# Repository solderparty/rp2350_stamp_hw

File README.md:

# The RP2350 Stamp

The Stamp was created to allow you to use the **Raspberry Pi RP2350A** in your designs without having to solder small-pitch QFN chips or worry about lots of external circuitry.

The RP2350 Stamp is pad-compatible with our previous RP2040 Stamp.

All you need to get you started is a 5V supply or a LiPo battery. The Stamp will take care of the charging and switching the power sources.

The castellated edges with **2mm pitch** can be hand-soldered directly to a Carrier board, used with pin headers for more flexibility, or connected without soldering using [FlexyPins](https://flexypin.solder.party), which are spring connectors designed for modules with castellated edges. You can find footprints for many PCB programs [here](https://github.com/solderparty/rp2xxx_stamp_footprints).

At only **1 by 1 inch**, the Stamp packs a lot of features:
* **16MB of FLASH**
* **500mA 3.3V LDO**
* **All 30 GPIOs broken out**
* LiPo supply and charging circuit (with charging LED)
* USB broken out
* SWD broken out
* Reset Button
* Bootsel Button
* 12MHz crystal

and of course, everything that comes with the Raspberry Pi RP2350 itself:
* Dual core ARM Cortex-M33 or Hazard3 @ 150MHz
* 520kB SRAM
* 2 UARTs
* 2 SPIs
* 2 I2Cs
* 24 PWM channels
* 12 PIO state machines
* 1 HSTX peripheral
* USB with Host and Device support

The RP2350 comes with a pre-programmed ROM UF2 Bootloader, by pulling the BOOTSEL pin low and resetting, or by double-pressing the RESET button (if the FW supports it), you can upload new firmware using the USB disk drive.

In addition to the Stamps we also offer a few reference designs, see the Carriers in the [Stamp-related category](https://docs.solder.party/rp2xxx-stamp-related) as well as our [Flux projects](https://docs.solder.party/flux).

The CircuitPython firmware for the Stamp comes with a built-in board files for the Carriers, for example you can access the RP2040 Stamp Carrier pins and interfaces by using `import stamp_carrier_board as board`. See [here](https://github.com/adafruit/circuitpython/tree/main/ports/raspberrypi/boards/solderparty_rp2040_stamp) for all the available Carrier board files.

# Links

For more information visit https://rp2350-stamp.solder.party/

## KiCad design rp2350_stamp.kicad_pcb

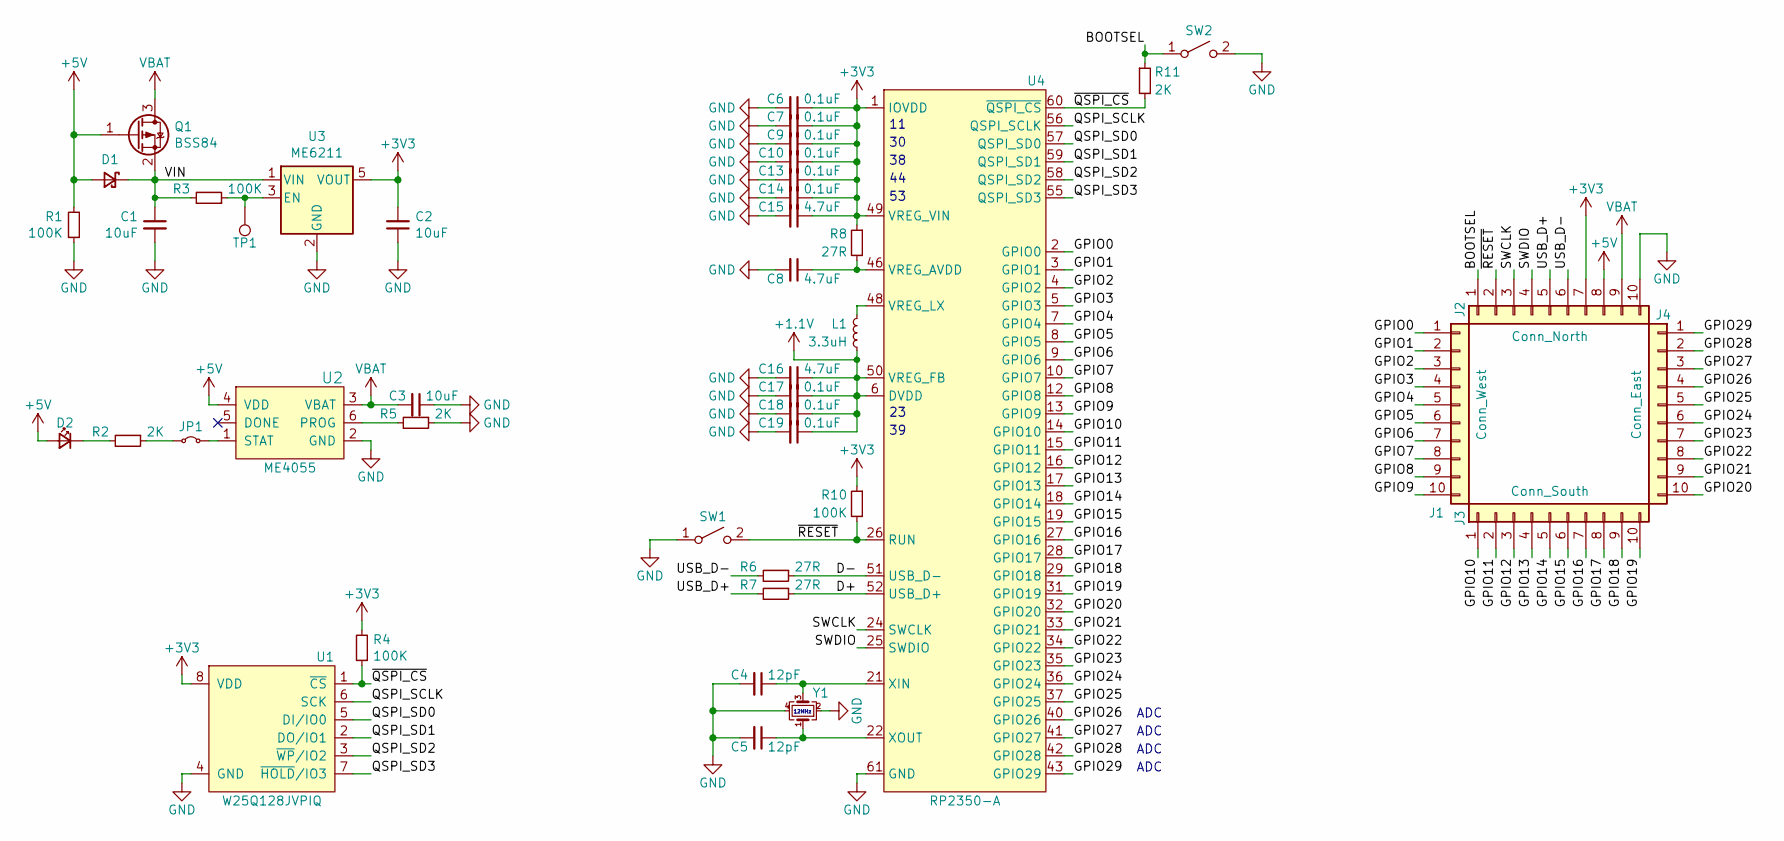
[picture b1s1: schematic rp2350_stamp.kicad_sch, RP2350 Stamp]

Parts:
C1, C2, C3: 10uF; C_0603_1608Metric
C4, C5: 12pF; C_0603_1608Metric
C6, C7, C9, C10, C13, C14, C17, C18, C19: 0.1uF; C_0603_1608Metric
C8, C15, C16: 4.7uF; C_0603_1608Metric
D1: D_Schottky_Small; D_SOD-323; LCSC C114023
D2: LED_CHR; LED_0603_1608Metric
J1: Conn_West; Castellated_1x10_P2.00mm_Vertical
J2: Conn_North; Castellated_1x10_P2.00mm_Vertical
J3: Conn_South; Castellated_1x10_P2.00mm_Vertical
J4: Conn_East; Castellated_1x10_P2.00mm_Vertical
JP1: SJ_STAT_LED; SolderJumper-2_P1.3mm_Bridged_RoundedPad1.0x1.5mm
L1: 3.3uH; L_Wuerth_MAPI-2512; LCSC C5832359
Q1: BSS84; SOT-23; LCSC C85202
R1, R3, R4, R10: 100K; R_0603_1608Metric
R2, R5, R11: 2K; R_0603_1608Metric
R6, R7, R8: 27R; R_0603_1608Metric
SW1: SW_RESET; SW_SPST_B3U-1000P; LCSC C561514
SW2: SW_BOOTSEL; SW_SPST_B3U-1000P; LCSC C561514
TP1: TP_LDO_EN; TestPoint_Pad_D1.5mm
U1: W25Q128JVPIQ; WSON-8-1EP_6x5mm_P1.27mm_EP3.4x4mm; LCSC C190862
U2: ME4055; SOT-23-6; LCSC C82121
U3: ME6211; SOT-23-5; LCSC C82942
U4: RP2350-A; QFN-60_EP_7x7_Pitch0.4mm
Y1: CM4012M00012001; Crystal_SMD_2520-4Pin_2.5x2.0mm; LCSC C7294611

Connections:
+1.1V: C16.1, C17.1, C18.1, C19.1, L1.1, U4.6 (DVDD), U4.23 (DVDD), U4.39 (DVDD), U4.50 (VREG_FB)
+3V3: C2.2, C6.1, C7.1, C9.1, C10.1, C13.1, C14.1, C15.1, J2.7, R4.2, R8.1, R10.1, U1.8 (VDD), U3.5 (VOUT), U4.1 (IOVDD), U4.11 (IOVDD), U4.20 (IOVDD), U4.30 (IOVDD), U4.38 (IOVDD), U4.44 (IOVDD), U4.45 (IOVDD), U4.49 (VREG_VIN), U4.53 (IOVDD), U4.54 (IOVDD)
+5V: D1.2 (A), D2.2 (A), J2.8, Q1.1 (G), R1.2, U2.4 (VDD)
/BOOTSEL: J2.1, R11.1, SW2.1 (A)
/D+: R7.1, U4.52 (USB_D+)
/D-: R6.1, U4.51 (USB_D-)
/GPIO0: J1.1, U4.2 (GPIO0)
/GPIO1: J1.2, U4.3 (GPIO1)
/GPIO2: J1.3, U4.4 (GPIO2)
/GPIO3: J1.4, U4.5 (GPIO3)
/GPIO4: J1.5, U4.7 (GPIO4)
/GPIO5: J1.6, U4.8 (GPIO5)
/GPIO6: J1.7, U4.9 (GPIO6)
/GPIO7: J1.8, U4.10 (GPIO7)
/GPIO8: J1.9, U4.12 (GPIO8)
/GPIO9: J1.10, U4.13 (GPIO9)
/GPIO10: J3.1, U4.14 (GPIO10)
/GPIO11: J3.2, U4.15 (GPIO11)
/GPIO12: J3.3, U4.16 (GPIO12)
/GPIO13: J3.4, U4.17 (GPIO13)
/GPIO14: J3.5, U4.18 (GPIO14)
/GPIO15: J3.6, U4.19 (GPIO15)
/GPIO16: J3.7, U4.27 (GPIO16)
/GPIO17: J3.8, U4.28 (GPIO17)
/GPIO18: J3.9, U4.29 (GPIO18)
/GPIO19: J3.10, U4.31 (GPIO19)
/GPIO20: J4.10, U4.32 (GPIO20)
/GPIO21: J4.9, U4.33 (GPIO21)
/GPIO22: J4.8, U4.34 (GPIO22)
/GPIO23: J4.7, U4.35 (GPIO23)
/GPIO24: J4.6, U4.36 (GPIO24)
/GPIO25: J4.5, U4.37 (GPIO25)
/GPIO26: J4.4, U4.40 (GPIO26)
/GPIO27: J4.3, U4.41 (GPIO27)
/GPIO28: J4.2, U4.42 (GPIO28)
/GPIO29: J4.1, U4.43 (GPIO29)
/QSPI_SCLK: U1.6 (SCK), U4.56 (QSPI_SCLK)
/QSPI_SD0: U1.5 (DI/IO0), U4.57 (QSPI_SD0)
/QSPI_SD1: U1.2 (DO/IO1), U4.59 (QSPI_SD1)
/QSPI_SD2: U1.3 (~WP/IO2), U4.58 (QSPI_SD2)
/QSPI_SD3: U1.7 (~HOLD/IO3), U4.55 (QSPI_SD3)
/SWCLK: J2.3, U4.24 (SWCLK)
/SWDIO: J2.4, U4.25 (SWDIO)
/USB_D+: J2.5, R7.2
/USB_D-: J2.6, R6.2
/VIN: C1.1, D1.1 (K), Q1.2 (S), R3.2, U3.1 (VIN)
/~QSPI_CS: R4.1, R11.2, U1.1 (~CS), U4.60 (~QSPI_CS)
/~RESET: J2.2, R10.2, SW1.2 (B), U4.26 (RUN)
GND: C1.2, C2.1, C3.1, C4.2, C5.2, C6.2, C7.2, C8.2, C9.2, C10.2, C13.2, C14.2, C15.2, C16.2, C17.2, C18.2, C19.2, J2.10, R1.1, R5.1, SW1.1 (A), SW2.2 (B), U1.4 (GND), U1.9 (GND), U2.2 (GND), U3.2 (GND), U4.47 (GND), U4.61 (GND), Y1.2, Y1.4
unnamed: D2.1 (K), R2.2
unnamed: JP1.1 (A), R2.1
unnamed: JP1.2 (B), U2.1 (STAT)
unnamed: R5.2, U2.6 (PROG)
unnamed: R3.1, TP1.1, U3.3 (EN)
unnamed: C8.1, R8.2, U4.46 (VREG_AVDD)
unnamed: L1.2, U4.48 (VREG_LX)
unnamed: C4.1, U4.21 (XIN), Y1.3
unnamed: C5.1, U4.22 (XOUT), Y1.1
VBAT: C3.2, J2.9, Q1.3 (D), U2.3 (VBAT)

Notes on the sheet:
ADC
12MHz

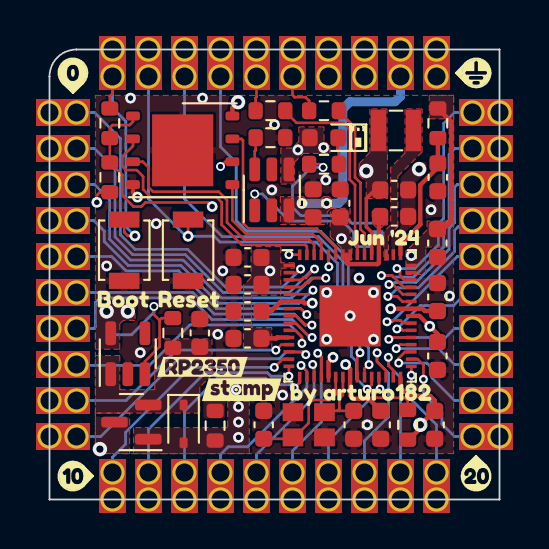
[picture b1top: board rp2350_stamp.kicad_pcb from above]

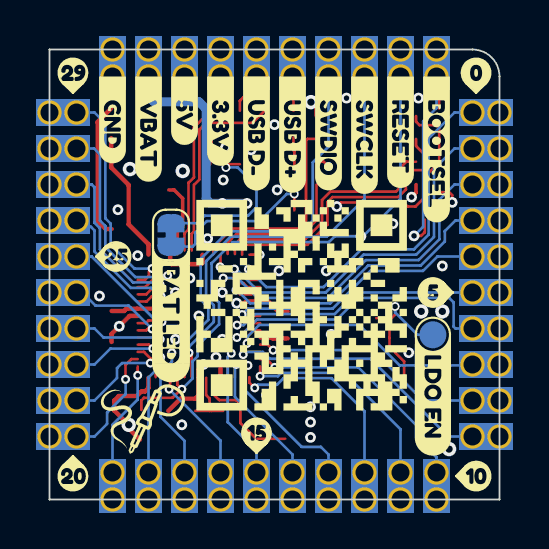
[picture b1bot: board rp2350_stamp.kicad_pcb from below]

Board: 4 copper layers, 25.0 x 25.0 mm, 74 parts (23 on the bottom side), 59 nets.

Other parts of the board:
kibuzzard-65C79539: G***; kibuzzard-65C79539
kibuzzard-6577C6A3: G***; kibuzzard-6577C6A3
kibuzzard-6577C69C: G***; kibuzzard-6577C69C
kibuzzard-6578FB5D: G***; kibuzzard-6578FB5D
kibuzzard-6578FB6C: G***; kibuzzard-6578FB6C
kibuzzard-6578FB20: G***; kibuzzard-6578FB20
kibuzzard-6578FB80: G***; kibuzzard-6578FB80
kibuzzard-6578FBA5: G***; kibuzzard-6578FBA5
kibuzzard-6578FBB3: G***; kibuzzard-6578FBB3
kibuzzard-6578FBCE: G***; kibuzzard-6578FBCE
kibuzzard-6578FC1D: G***; kibuzzard-6578FC1D
kibuzzard-6578FC06: G***; kibuzzard-6578FC06
kibuzzard-6578FC10: G***; kibuzzard-6578FC10
kibuzzard-6578FE34: G***; kibuzzard-6578FE34
kibuzzard-6605AA87: G***; kibuzzard-6605AA87
kibuzzard-6605AAE9: G***; kibuzzard-6605AAE9
kibuzzard-6605B0A1: G***; kibuzzard-6605B0A1
kibuzzard-6605B0D5: G***; kibuzzard-6605B0D5
kibuzzard-6695A5B8: G***; kibuzzard-6695A5B8
kibuzzard-6695A66B: G***; kibuzzard-6695A66B
kibuzzard-6695ACF2, kibuzzard-6695ACF2#2: G***; kibuzzard-6695ACF2
kibuzzard-6695AD2C, kibuzzard-6695AD2C#2: G***; kibuzzard-6695AD2C
kibuzzard-6695AD18, kibuzzard-6695AD18#2: G***; kibuzzard-6695AD18
kibuzzard-6695B1B2: G***; kibuzzard-6695B1B2
kibuzzard-6695B2B8: G***; kibuzzard-6695B2B8
kibuzzard-6695B237: G***; kibuzzard-6695B237
kibuzzard-6695B350: G***; kibuzzard-6695B350

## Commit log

2023-12-13 Rev 1
2024-02-11 Rev 2
    Swapped back to SOT-23 LiPo charger
    Added QR Code
    Added LDO EN back silk
    Moved around front silk
2024-03-28 Rev 3
    Added a solder jumper for BAT LED
2024-07-16 Rev 4
    - Put chip name on the board
    - Fixup pin markers to be uniform
2024-07-28 Rev 4.5
    Fixup power stuff according to RPi's recommendations
2024-10-01 Fix BOM info, add README and LICENSE
